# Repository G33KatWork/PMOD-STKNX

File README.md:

STKNX Pmod
==========

**WARNING**: See [known issues](#known-issues) before ordering boards!

This is a small breakout board for an ST microelectronics [STKNX KNX line transceiver](https://www.st.com/en/interfaces-and-transceivers/stknx.html)

Hardware
--------

The board is currently being manufactured and the design has briefly been powered up and tested - it didn't go up in flames... yet. It is very close to the ST reference design of the EVALKITSTKNX development board, just without the microcontroller

The STKNX is not a full KNX MAC. It is only a line transceiver that performs some KNX bus compliant signal conditioning and also delivers power using its voltage regulators from the bus to the device.

There is no real open source software support right now for bit-banging the KNX protocol using this transceiver. It is very useful to perform sniffing tasks on the bus if you are interested in the raw bits that are sent.

Known issues
------------

The polarization of the KNX connector is wrong. It's a pretty dumb mistake, but oh well, it happened.

Possible solutions:

1. Don't care, connect the red wire to the black terminal and vice versa
2. Don't care like in 1) but use the yellow/white WAGO terminal to make sure you remember to swap the polarity
3. Take apart a WAGO terminal by force and swap the black and red terminal
4. Solder the pins on the bottom of the board and plug the WAGO terminal in there.
5. Cut the GND connections on the one pin, cut the bus connection on the other pin and bodge the GND and bus connection to the right pins
6. Fix it in the board design, reorder and rebuild the boards

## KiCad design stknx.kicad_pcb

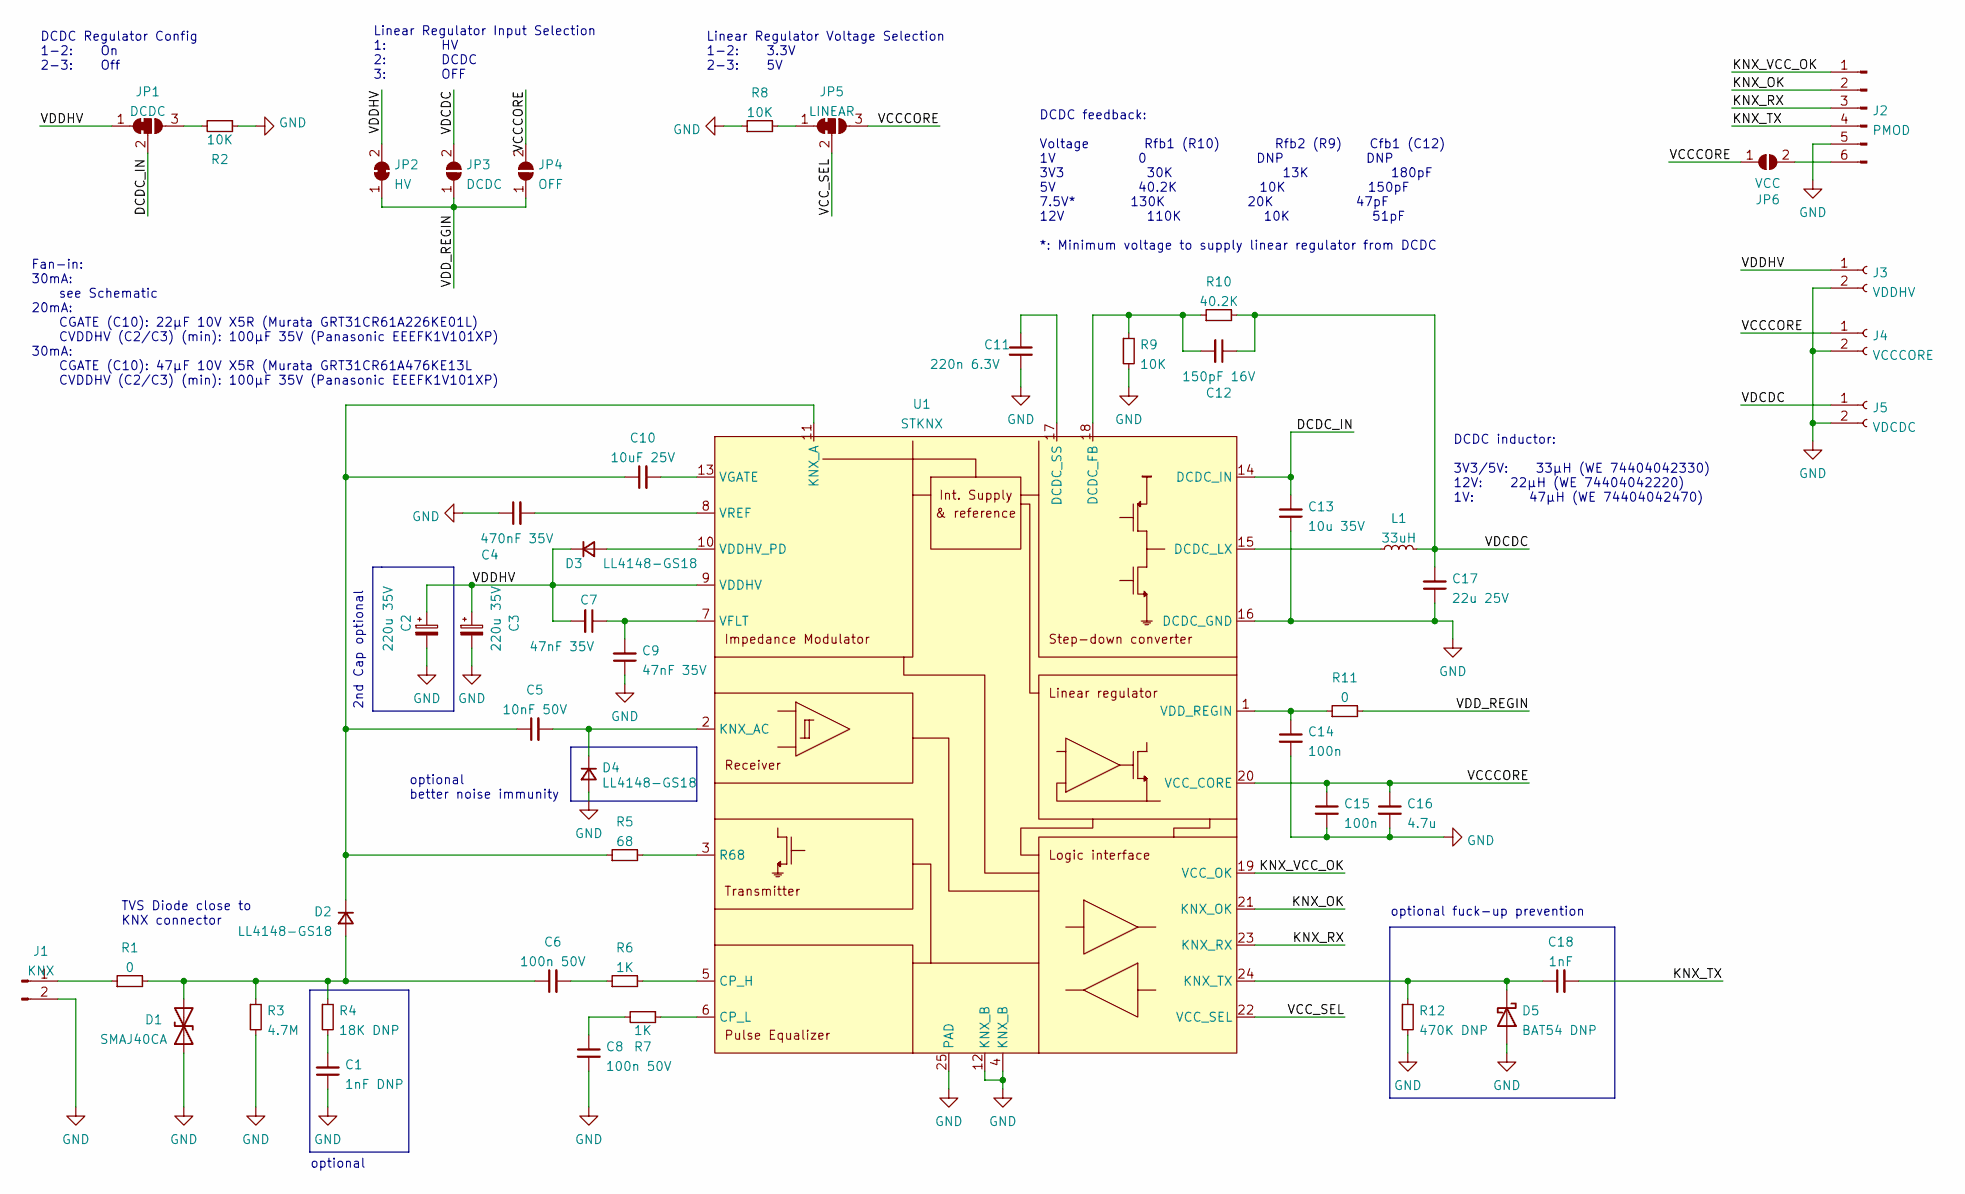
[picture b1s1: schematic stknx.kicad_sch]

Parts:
C1: 1nF DNP; C_0402_1005Metric; Part Description 1000pF ±10% 50V Ceramic Capacitor X7R 0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
C2, C3: 220u 35V; C_Elec_10x10.2; Part Description 220µF 50V Aluminum Electrolytic Capacit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
C4: 470nF 35V; C_0805_2012Metric; Part Description 0.47µF ±10% 50V Ceramic Capacitor X7R 0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
C5: 10nF 50V; C_0402_1005Metric; Part Description 10000pF ±10% 50V Ceramic Capacitor X7R 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
C6, C8: 100n 50V; C_0603_1608Metric; Part Description 0.1µF ±10% 50V Ceramic Capacitor X7R 06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
C7, C9: 47nF 35V; C_0402_1005Metric; Part Description 0,047µF ±10% 50V Keramikkondensatoren X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
C10: 10uF 25V; C_1206_3216Metric; Part Description 10µF ±10% 25V Ceramic Capacitor X7R 120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
C11: 220n 6.3V; C_0402_1005Metric; Part Description 0.22µF ±10% 10V Ceramic Capacitor X7R 0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
C12: 150pF 16V; C_0402_1005Metric; Part Description 150pF ±10% 16V Ceramic Capacitor X7R 04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
C13: 10u 35V; C_1206_3216Metric; Part Description 10µF ±10% 35V Ceramic Capacitor X5R 120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
C14, C15: 100n; C_0402_1005Metric; Part Description 0.1µF ±10% 25V Ceramic Capacitor X7R 04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
C16: 4.7u; C_0805_2012Metric; Part Description 4.7µF ±10% 6.3V Ceramic Capacitor X7R 0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
C17: 22u 25V; C_1210_3225Metric; Part Description 22µF ±20% 25V Ceramic Capacitor X7R 121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
C18: 1nF; C_0402_1005Metric; Part Description 1000pF ±10% 50V Ceramic Capacitor X7R 0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
D1: SMAJ40CA; D_SMA; Part Description 64.5V Clamp 6.2A Ipp Tvs Diode Surface 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
D2, D3, D4: LL4148-GS18; D_MiniMELF; Part Description Diode Standard 75V 300mA (DC) Surface M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
D5: BAT54 DNP; D_SOD-323F; Part Description Diode Schottky 30V 200mA Surface Mount 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
J1: KNX; WAGO_243-211; Part Description KNX Klemme Stifte, 2x
J2: PMOD; PinHeader_1x06_P2.54mm_Horizontal; Part Description Connector Header Through Hole, Right An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
J3: VDDHV; PinHeader_1x02_P2.54mm_Vertical
J4: VCCCORE; PinHeader_1x02_P2.54mm_Vertical
J5: VDCDC; PinHeader_1x02_P2.54mm_Vertical
JP1: DCDC; SolderJumper-3_P1.3mm_Open_RoundedPad1.0x1.5mm_NumberLabels
JP2: HV; SolderJumper-2_P1.3mm_Open_RoundedPad1.0x1.5mm
JP3: DCDC; SolderJumper-2_P1.3mm_Open_RoundedPad1.0x1.5mm
JP4: OFF; SolderJumper-2_P1.3mm_Open_RoundedPad1.0x1.5mm
JP5: LINEAR; SolderJumper-3_P1.3mm_Open_RoundedPad1.0x1.5mm_NumberLabels
JP6: VCC; SolderJumper-2_P1.3mm_Open_RoundedPad1.0x1.5mm
L1: 33uH; L_WE_LQS_4012; Part Description 33µH Semi-Shielded Wirewound Inductor 6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
R1, R11: 0; R_0402_1005Metric; Part Description 0 Ohms Jumper 0.063W, 1/16W Chip Resist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
R2, R8: 10K; R_0402_1005Metric; Part Description 10 kOhms ±5% 0.063W, 1/16W Chip Resisto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
R3: 4.7M; R_0402_1005Metric; Part Description 4.7 MOhms ±1% 0.063W, 1/16W Chip Resist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
R4: 18K DNP; R_0402_1005Metric; Part Description 18 kOhms ±1% 0.063W, 1/16W Chip Resisto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
R5: 68; R_2512_6332Metric; Part Description 68 Ohms ±1% 1W Chip Resistor 2512 (6432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
R6, R7: 1K; R_0402_1005Metric; Part Description 1 kOhms ±1% 0.063W, 1/16W Chip Resistor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
R9: 10K; R_0402_1005Metric; Part Description 10 kOhms ±0.1% 0.063W, 1/16W Chip Resis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
R10: 40.2K; R_0402_1005Metric; Part Description 40.2 kOhms ±0.1% 0.063W, 1/16W Chip Res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
R12: 470K DNP; R_0402_1005Metric; Part Description 470 kOhms ±1% 0.063W, 1/16W Chip Resist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
U1: STKNX; VQFN-24-1EP_4x4mm_P0.5mm_EP2.45x2.45mm; Part Description 0/1 Transceiver 24-VFQFPN (4x4)

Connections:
/DCDC_IN: C13.2, JP1.2 (C), U1.14 (DCDC_IN)
/KNX_OK: J2.2, U1.21 (KNX_OK)
/KNX_RX: J2.3, U1.23 (KNX_RX)
/KNX_TX: C18.2, J2.4
/KNX_VCC_OK: J2.1, U1.19 (VCC_OK)
/VCCCORE: C15.1, C16.1, J4.1, JP4.2 (B), JP5.3 (B), JP6.1 (A), U1.20 (VCC_CORE)
/VCC_SEL: JP5.2 (C), U1.22 (VCC_SEL)
/VDCDC: C12.1, C17.2, J5.1, JP3.2 (B), L1.2, R10.2
/VDDHV: C2.1, C3.1, C7.2, D3.1 (K), J3.1, JP1.1 (A), JP2.2 (B), U1.9 (VDDHV)
/VDD_REGIN: JP2.1 (A), JP3.1 (A), JP4.1 (A), R11.2
GND: C1.1, C2.2, C3.2, C4.1, C8.2, C9.1, C11.2, C13.1, C14.2, C15.2, C16.2, C17.1, D1.1 (A1), D4.2 (A), D5.2 (A), J1.2, J2.5, J3.2, J4.2, J5.2, R2.1, R3.2, R8.1, R9.2, R12.2, U1.4 (KNX_B), U1.12 (KNX_B), U1.16 (DCDC_GND), U1.25 (PAD)
unnamed: C1.2, R4.2
unnamed: C4.2, U1.8 (VREF)
unnamed: C5.2, D4.1 (K), U1.2 (KNX_AC)
unnamed: C6.1, D1.2 (A2), D2.2 (A), R1.2, R3.1, R4.1
unnamed: C6.2, R6.1
unnamed: C7.1, C9.2, U1.7 (VFLT)
unnamed: C8.1, R7.2
unnamed: C5.1, C10.1, D2.1 (K), R5.1, U1.11 (KNX_A)
unnamed: C10.2, U1.13 (VGATE)
unnamed: C11.1, U1.17 (DCDC_SS)
unnamed: C12.2, R9.1, R10.1, U1.18 (DCDC_FB)
unnamed: C14.1, R11.1, U1.1 (VDD_REGIN)
unnamed: C18.1, D5.1 (K), R12.1, U1.24 (KNX_TX)
unnamed: D3.2 (A), U1.10 (VDDHV_PD)
unnamed: J1.1, R1.1
unnamed: J2.6, JP6.2 (B)
unnamed: JP1.3 (B), R2.2
unnamed: JP5.1 (A), R8.2
unnamed: L1.1, U1.15 (DCDC_LX)
unnamed: R5.2, U1.3 (R68)
unnamed: R6.2, U1.5 (CP_H)
unnamed: R7.1, U1.6 (CP_L)

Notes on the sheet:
Fan-in: 30mA: see Schematic 20mA: CGATE (C10): 22µF 10V X5R (Murata GRT31CR61A226KE01L) CVDDHV (C2/C3) (min): 100µF 35V (Panasonic EEEFK1V101XP) 30mA: CGATE (C10): 47µF 10V X5R (Murata GRT31CR61A476KE13L CVDDHV (C2/C3) (min): 100µF 35V (Panasonic EEEFK1V101XP)
DCDC Regulator Config 1-2: On 2-3: Off
TVS Diode close to KNX connector
optional
2nd Cap optional
Linear Regulator Input Selection 1: HV 2: DCDC 3: OFF
optional better noise immunity
Linear Regulator Voltage Selection 1-2: 3.3V 2-3: 5V
DCDC feedback: Voltage Rfb1 (R10) Rfb2 (R9) Cfb1 (C12) 1V 0 DNP DNP 3V3 30K 13K 180pF 5V 40.2K 10K 150pF 7.5V* 130K 20K 47pF 12V 110K 10K 51pF *: Minimum voltage to supply linear regulator from DCDC
optional fuck-up prevention
DCDC inductor: 3V3/5V: 33µH (WE 74404042330) 12V: 22µH (WE 74404042220) 1V: 47µH (WE 74404042470)

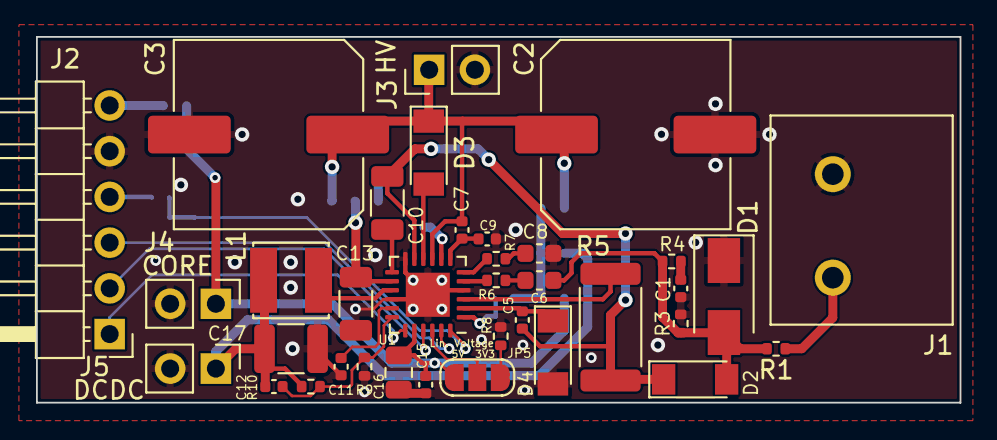
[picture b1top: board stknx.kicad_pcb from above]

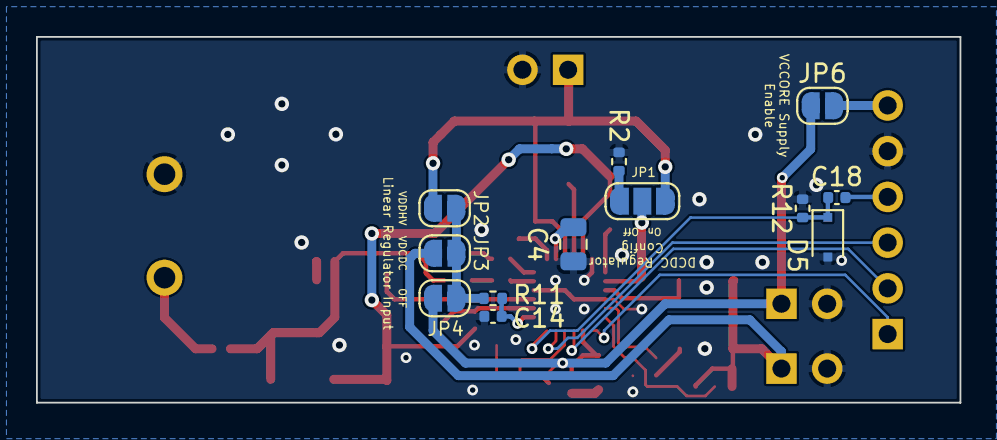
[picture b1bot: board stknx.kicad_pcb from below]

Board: 2 copper layers, 51.3 x 20.3 mm, 48 parts (12 on the bottom side), 33 nets.

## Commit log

2021-09-17 Initial import
2021-09-17 Fix things
2021-09-17 Make R5 not go up in flames once we transmit the first bit
2021-09-17 Rotate D4
2021-09-17 BAT54
2021-09-17 Inductor footprint
2021-09-18 Rough component placement
2021-09-20 First attempts at routing
2021-09-20 Minor fixes
2021-09-20 Silkscreen
2021-09-20 A few DRC fixes
2021-09-20 improve GND connectivity a bit
2021-09-20 make power trace width more consistent
2021-09-20 reroute with jlc specs
2021-09-20 via size fasching and some GND optimization
2021-09-21 fix U1 pin 4 connectivity
2021-09-25 Remove default-jumpers and replace them with open jumpers to avoid the need to scratch around on that beatiful PCB
2021-09-25 Silkscreen for JP5
2021-11-05 Add Gerbers
2021-11-05 Add schematic and PCB renderings for posing on Twitter
2021-11-05 Readme
2022-01-25 Document known issues
